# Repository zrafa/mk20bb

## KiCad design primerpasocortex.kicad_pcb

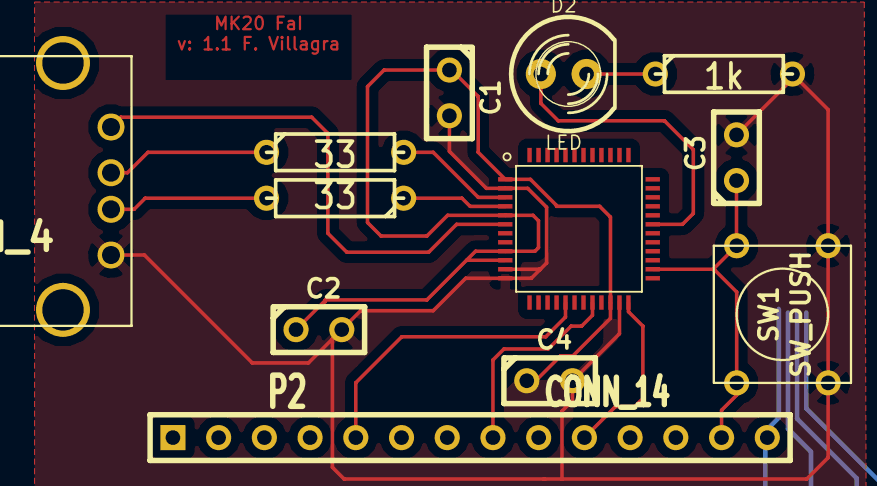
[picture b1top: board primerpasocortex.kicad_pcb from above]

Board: 2 copper layers, 12 parts (0 on the bottom side), 13 nets.

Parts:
C1, C2, C3, C4: 100n; C1
D2: LED; LED-5MM
LQFP48: Val*; LQFP48
P1: CONN_4; USB_A
P2: CONN_14; SIL-14
R2, R3: 33; R3
R4: 1k; R3
SW1: SW_PUSH; SW_PUSH_SMALL

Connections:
unnamed: LQFP48.6, P1.1
unnamed: D2.2, R4.1
unnamed: D2.1, LQFP48.31
unnamed: C3.1, LQFP48.26, P2.13, SW1.1
unnamed: C1.2, C2.2, C3.2, C4.2, LQFP48.2, LQFP48.11, LQFP48.12, LQFP48.23, P1.4, R4.2, SW1.2
unnamed: C1.1, C2.1, C4.1, LQFP48.1, LQFP48.5, LQFP48.9, LQFP48.10, LQFP48.22
unnamed: LQFP48.24, P2.10
unnamed: P1.2, R2.1
unnamed: P1.3, R3.2
unnamed: LQFP48.17, P2.5
unnamed: LQFP48.3, R2.2
unnamed: LQFP48.4, R3.1
unnamed: LQFP48.20, P2.8

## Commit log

2015-10-26 primera version del proyecto
2015-10-28 librerias
2015-10-31 agrego .net .lst y .drl
2015-10-31 modificaciones en plano masa
